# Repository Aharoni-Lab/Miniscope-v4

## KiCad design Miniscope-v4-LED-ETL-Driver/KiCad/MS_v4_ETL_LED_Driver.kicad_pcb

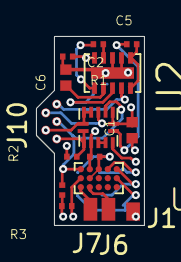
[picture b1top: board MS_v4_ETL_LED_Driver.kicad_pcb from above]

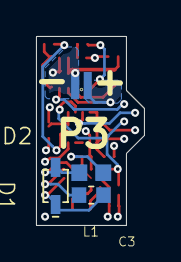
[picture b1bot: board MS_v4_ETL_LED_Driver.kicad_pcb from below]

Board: 6 copper layers, 6.0 x 10.5 mm, 20 parts (4 on the bottom side), 16 nets.

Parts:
C1, C6: GRM155R60J475ME87D; C_0402_1005Metric_L
C2, C5: GRM033R61A225ME47D; C_0201_0603Metric_L
C3: 100nF 100V 0603; C_0603_1608Metric_L
C4, C7: GRM033R61A104ME15D; C_0201_0603Metric_L
D1: BAS316; SOD_323_250X125X110L30X32L
D2: LXZ1-PR01; LED_LXZ1_PR01_L
J1, J6, J7: Conn_01x01; Conn_1x1_250x750_Pad
J10: Conn_01x05; B2B_Flex_05_Dual_Row_38milx24mil_Pad_20mil
L1: LQM18PN3R3MGHD; L_0603_1608Metric_L
R1, R2, R3: ERJ-1GEF1022C; R_0201_0603Metric_ERJ_L
U1: MAX14574EWL+; BGA_15_NP50_3X5_155X255X69B31N
U2: TPL0102-100RUCR; QFN_14_P40_200X200X40L40X20L
U3: LTC3218; SON_11_P50_300X200X80L40X25T239X64L

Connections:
+3V3: C1.1, C2.1, C4.1, C7.1, J10.5, L1.1, R2.2, R3.2, U1.A3, U1.B2, U2.1, U2.14, U3.10
/ENT: J10.1, U3.4
/EWL1: J6.1, U1.C2
/EWL2: J7.1, U1.C1
/I_SET: R1.2, U3.5, U3.6
/SCL: J10.2, R3.1, U1.B1, U2.10
/SDA: J10.3, R2.1, U1.A1, U2.9
GND: C1.2, C2.2, C3.2, C4.2, C6.2, C7.2, D2.C, J1.1, J10.4, U1.A2, U1.A5, U2.2, U2.5, U2.7, U2.8, U2.11, U2.12, U2.13, U3.7, U3.8, U3.11
unnamed: C3.1, D1.C, U1.B5
unnamed: C5.1, U3.9
unnamed: C5.2, U3.1
unnamed: C6.1, U3.2
unnamed: D1.A, L1.2, U1.A4
unnamed: D2.A, U3.3
unnamed: R1.1, U2.6
unnamed: U2.3, U2.4
